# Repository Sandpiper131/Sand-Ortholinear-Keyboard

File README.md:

# [ Description ]
The Sand Ortholinear is a QWERTY style keyboard with 47 individually programmable keys. The
keyboard is powered by an ATMEGA32U4 microcontroller running the QMK open source keyboard
firmware. The goal of this project was to design a keyboard which is compact and durable while
having a simple case.

# [ Design Requirements ]
-Compact/Portable  
-Cherry MX Compatible  
-Ortholinear QWERTY (Grid) Layout with 2U spacebar  
-No visible components on top side of board  
-minimize trace presence on visible portions of top PCB  
-Sandwich style case PCB|ACRYLIC|PCB held together with M3 Screws  
-USB-C Connector  
-Sturdy Construction  

# [ Gallery ]
## Renders:
")  
")  

## Schematics:

## Board Layout:
")
")
")
")

## Pictures:

# [ Version History ]
## QMKDEVBRD
The QMK Development Board is a 3x3 Cherry MX-Compatible keypad used to
prototype a keyboard circuit prior to building a larger and more expensive keyboard. 
In addition to the basic microcontroller circuit with ISP and USB connectivity a 
prototyping area with breakouts for unused uC pins is included. Doing so 
makes this board not only a prototype for a final keyboard design, but also
a useful tool for contributing to the QMK Firmware project in the future.
The QMK Development Board functions as expected and works flawlessly with 
the QMK firmware. 

## Sand v1.0
Error in USB-C Circuit, no resistors for orientation, D+/D- not shorted 
to respective pair; USB connectivity non-functional. Added protection
circuit with Schottkey Diode and PTC fuse. Diodes are too small and
difficult to solder resulting in feedback in keyboard matrix. Crystal
Oscillator is also too small and impossible to solder by hand; Resolved
using a through hole crystal soldered onto pads. 

Changing focus to the mechanical/visual design of the keyboard is a simple
yet elegant PCB and Acrylic sandwich all held togetherwith M3 bolts and nuts.  
The resulting keyboard exceeded expectations and is very rigid, low-profile,
and provides ample protection from dust and debris.

## Sand v1.1
Added larger surface mount crystal oscillator and corrected above mentioned
flaws in the USB-C circuit. Opted not to change the diodes
as this was a minor revision and the part had already been ordered in excess.

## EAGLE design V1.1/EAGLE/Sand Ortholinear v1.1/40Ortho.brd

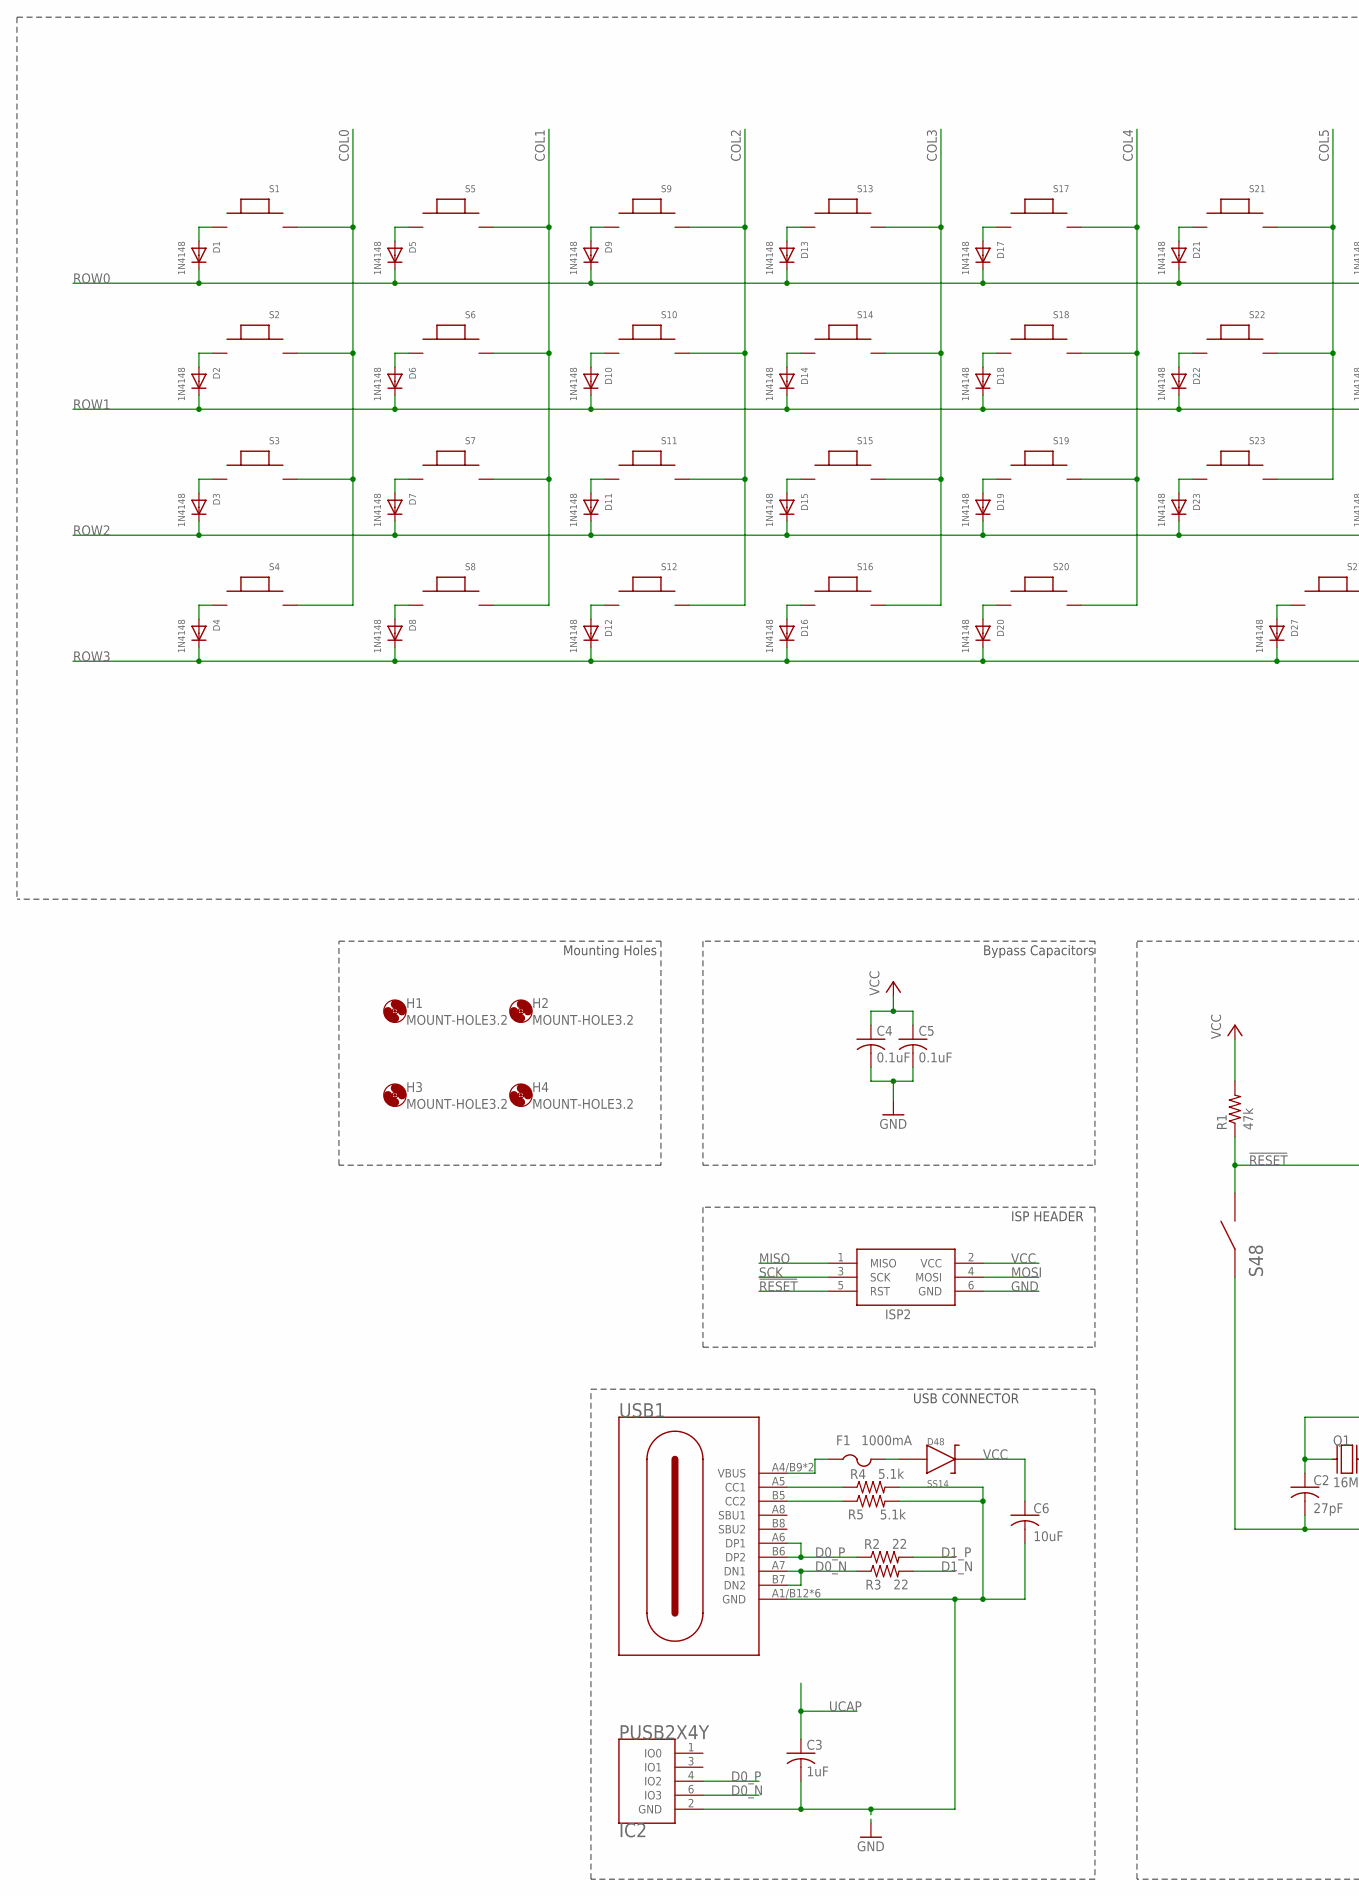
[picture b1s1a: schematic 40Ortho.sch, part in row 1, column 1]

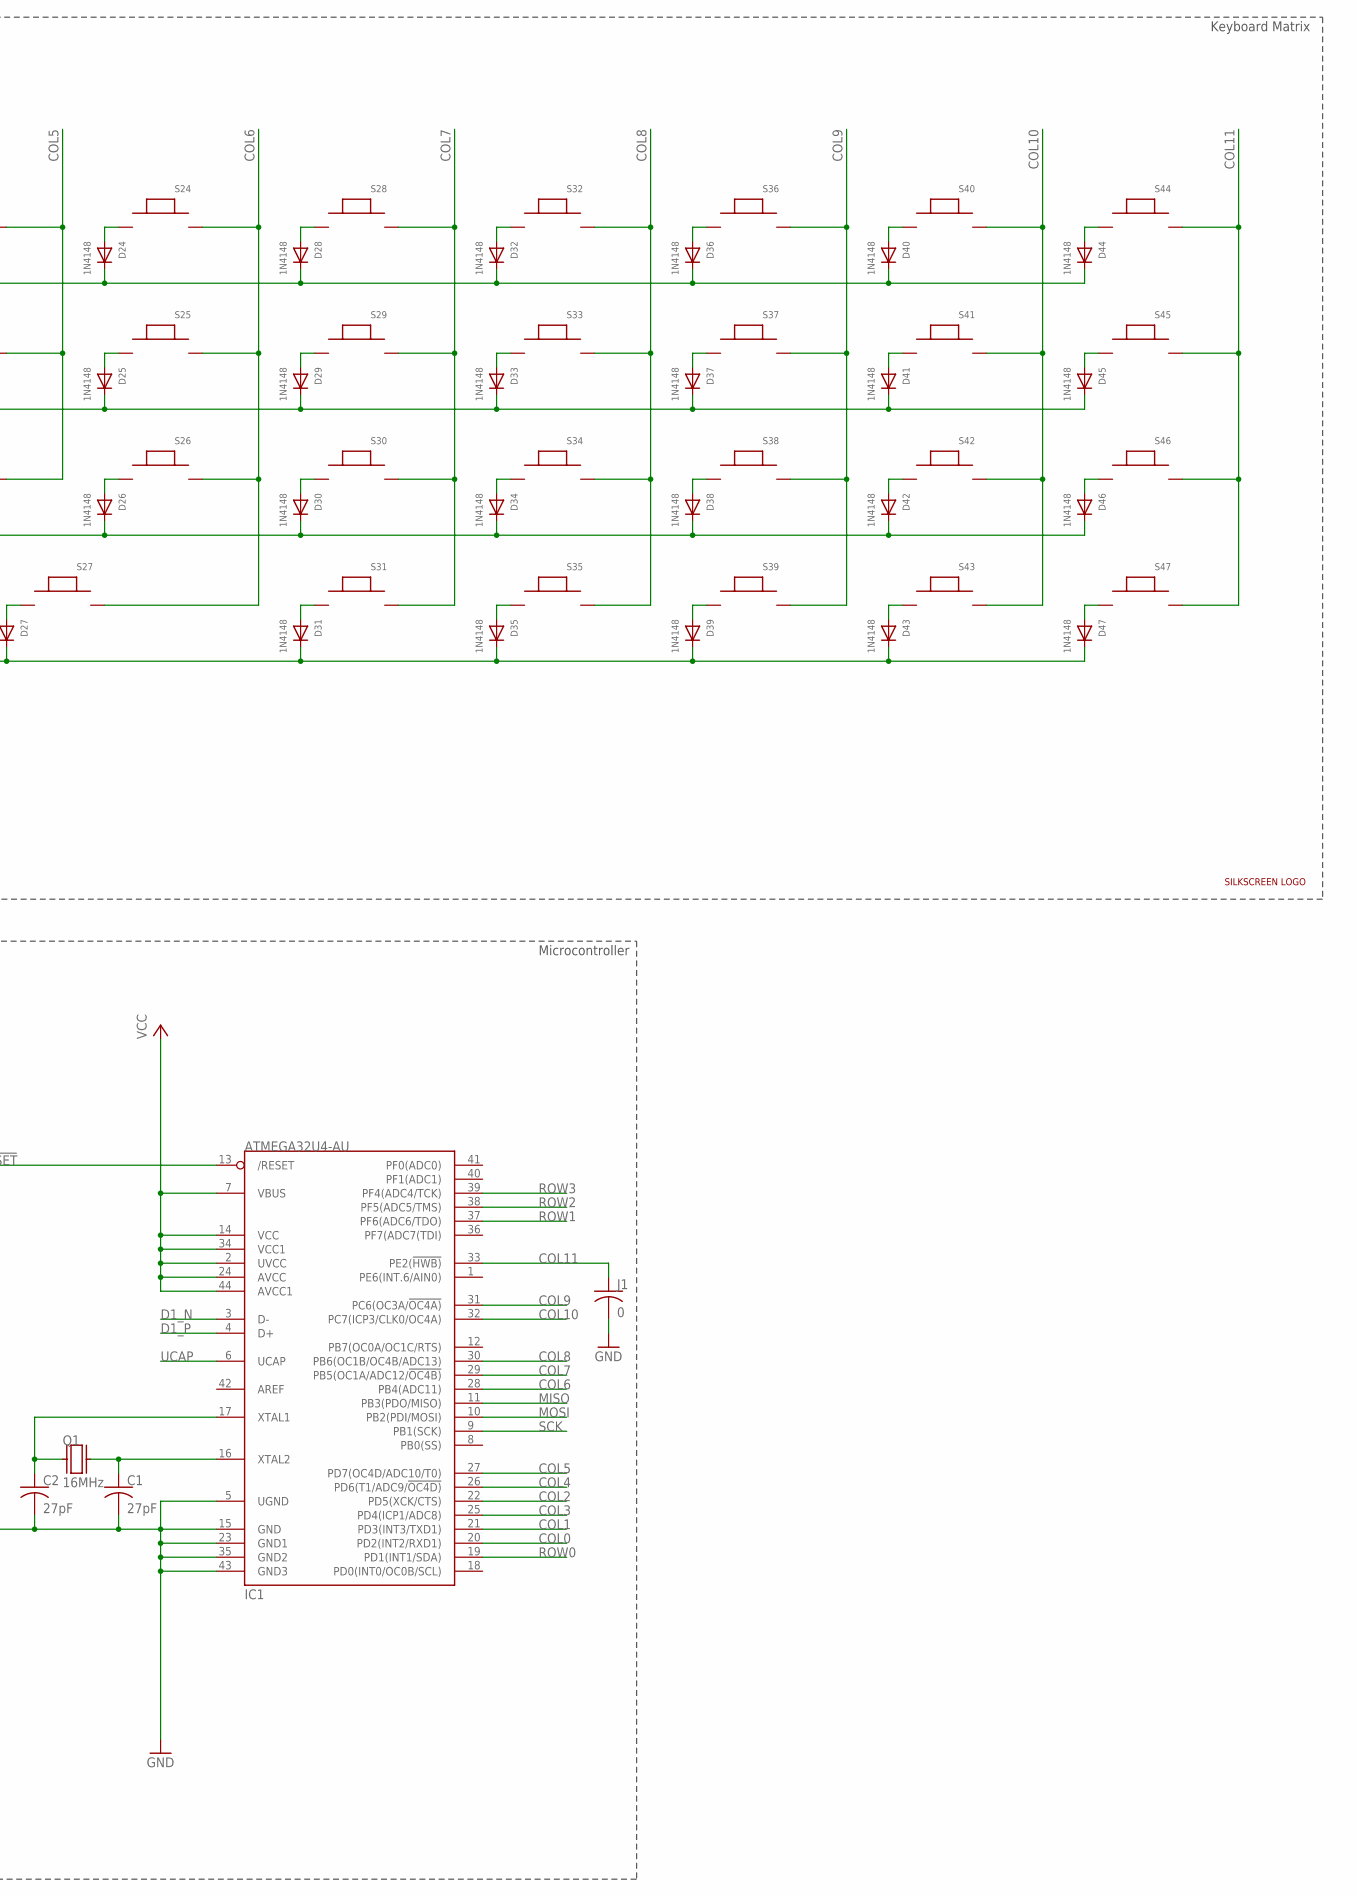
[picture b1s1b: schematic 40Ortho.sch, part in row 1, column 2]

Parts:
C1, C2: 27pF; C0805
C3: 1uF; C0805
C4, C5: 0.1uF; C0805
C6: 10uF; C0805
D1, D2, D3, D4, D5, D6, D7, D8, D9, D10, D11, D12, D13, D14, D15, D16, D17, D18, D19, D20, D21, D22, D23, D24, D25, D26, D27, D28, D29, D30, D31, D32, D33, D34, D35, D36, D37, D38, D39, D40, D41, D42, D43, D44, D45, D46, D47: 1N4148; SOD-323F
D48: SS14; DO-214AC
F1: 1000mA; R1206
H1, H2, H3, H4: MOUNT-HOLE3.2; 3,2
IC1: ATMEGA32U4-AU; TQFP44
IC2: PUSB2X4Y; SOT363
ISP2: AVRISP-6; AVRISP
J1: 0; C0805
Q1: 16MHz; ABLS7M2
R1: 47k; R0805
R2, R3: 22; R0805
R4, R5: 5.1k; R0805
S1, S2, S3, S4, S5, S6, S7, S8, S9, S10, S11, S12, S13, S14, S15, S16, S17, S18, S19, S20, S21, S22, S23, S24, S25, S26, S28, S29, S30, S31, S32, S33, S34, S35, S36, S37, S38, S39, S40, S41, S42, S43, S44, S45, S46, S47: MX_SMD_1U; MX_SMD
S27: MX_SMD_2UH; MX_SMD2U
S48: B3U-1000P
U$1: LOGO
USB1: USBC_16PINSMD

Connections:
!RESET: IC1.13 (/RESET), ISP2.5 (RST), R1.1, S48.2
COL0: IC1.20 (PD2(INT2/RXD1)), S1.P$2, S2.P$2, S3.P$2, S4.P$2
COL1: IC1.21 (PD3(INT3/TXD1)), S5.P$2, S6.P$2, S7.P$2, S8.P$2
COL2: IC1.22 (PD5(XCK/CTS)), S9.P$2, S10.P$2, S11.P$2, S12.P$2
COL3: IC1.25 (PD4(ICP1/ADC8)), S13.P$2, S14.P$2, S15.P$2, S16.P$2
COL4: IC1.26 (PD6(T1/ADC9/!OC4D)), S17.P$2, S18.P$2, S19.P$2, S20.P$2
COL5: IC1.27 (PD7(OC4D/ADC10/T0)), S21.P$2, S22.P$2, S23.P$2
COL6: IC1.28 (PB4(ADC11)), S24.P$2, S25.P$2, S26.P$2, S27.P$2
COL7: IC1.29 (PB5(OC1A/ADC12/!OC4B)), S28.P$2, S29.P$2, S30.P$2, S31.P$2
COL8: IC1.30 (PB6(OC1B/OC4B/ADC13)), S32.P$2, S33.P$2, S34.P$2, S35.P$2
COL9: IC1.31 (PC6(OC3A/!OC4A)), S36.P$2, S37.P$2, S38.P$2, S39.P$2
COL10: IC1.32 (PC7(ICP3/CLK0/OC4A)), S40.P$2, S41.P$2, S42.P$2, S43.P$2
COL11: IC1.33 (PE2(!HWB)), J1.1, S44.P$2, S45.P$2, S46.P$2, S47.P$2
D0_N: IC2.6 (IO3), R3.1, USB1.A7 (DN1), USB1.B7 (DN2)
D0_P: IC2.4 (IO2), R2.1, USB1.A6 (DP1), USB1.B6 (DP2)
D1_N: IC1.3 (D-), R3.2
D1_P: IC1.4 (D+), R2.2
GND: C1.2, C2.2, C3.2, C4.2, C5.2, C6.2, IC1.5 (UGND), IC1.15 (GND), IC1.23 (GND1), IC1.35 (GND2), IC1.43 (GND3), IC2.2 (GND), ISP2.6 (GND), J1.2, R4.2, R5.2, S48.1, USB1.A1/B12 (GND), USB1.B1/A12 (GND), USB1.GND@1 (GND), USB1.GND@2 (GND), USB1.GND@3 (GND), USB1.GND@4 (GND)
MISO: IC1.11 (PB3(PDO/MISO)), ISP2.1 (MISO)
MOSI: IC1.10 (PB2(PDI/MOSI)), ISP2.4 (MOSI)
unnamed: D32.A, S32.P$1
unnamed: D33.A, S33.P$1
unnamed: D34.A, S34.P$1
unnamed: D35.A, S35.P$1
unnamed: D36.A, S36.P$1
unnamed: D37.A, S37.P$1
unnamed: D38.A, S38.P$1
unnamed: D8.A, S8.P$1
unnamed: D40.A, S40.P$1
unnamed: D1.A, S1.P$1
unnamed: D2.A, S2.P$1
unnamed: D3.A, S3.P$1
unnamed: D4.A, S4.P$1
unnamed: D41.A, S41.P$1
unnamed: D5.A, S5.P$1
unnamed: D6.A, S6.P$1
unnamed: D9.A, S9.P$1
unnamed: D10.A, S10.P$1
unnamed: D7.A, S7.P$1
unnamed: D12.A, S12.P$1
unnamed: D42.A, S42.P$1
unnamed: D11.A, S11.P$1
unnamed: F1.1, USB1.A4/B9 (VBUS), USB1.B4/A9 (VBUS)
unnamed: D39.A, S39.P$1
unnamed: D13.A, S13.P$1
unnamed: D14.A, S14.P$1
unnamed: D15.A, S15.P$1
unnamed: D16.A, S16.P$1
unnamed: D44.A, S44.P$1
unnamed: D17.A, S17.P$1
unnamed: D18.A, S18.P$1
unnamed: D19.A, S19.P$1
unnamed: D20.A, S20.P$1
unnamed: D45.A, S45.P$1
unnamed: D21.A, S21.P$1
unnamed: D22.A, S22.P$1
unnamed: D23.A, S23.P$1
unnamed: D48.1 (ANODE), F1.2
unnamed: D46.A, S46.P$1
unnamed: D24.A, S24.P$1
unnamed: D25.A, S25.P$1
unnamed: D26.A, S26.P$1
unnamed: R4.1, USB1.A5 (CC1)
unnamed: D28.A, S28.P$1
unnamed: D29.A, S29.P$1
unnamed: D30.A, S30.P$1
unnamed: D31.A, S31.P$1
unnamed: R5.1, USB1.B5 (CC2)
unnamed: D27.A, S27.P$1
unnamed: D43.A, S43.P$1
unnamed: D47.A, S47.P$1
ROW0: D1.C, D5.C, D9.C, D13.C, D17.C, D21.C, D24.C, D28.C, D32.C, D36.C, D40.C, D44.C, IC1.19 (PD1(INT1/SDA))
ROW1: D2.C, D6.C, D10.C, D14.C, D18.C, D22.C, D25.C, D29.C, D33.C, D37.C, D41.C, D45.C, IC1.37 (PF6(ADC6/TDO))
ROW2: D3.C, D7.C, D11.C, D15.C, D19.C, D23.C, D26.C, D30.C, D34.C, D38.C, D42.C, D46.C, IC1.38 (PF5(ADC5/TMS))
ROW3: D4.C, D8.C, D12.C, D16.C, D20.C, D27.C, D31.C, D35.C, D39.C, D43.C, D47.C, IC1.39 (PF4(ADC4/TCK))
SCK: IC1.9 (PB1(SCK)), ISP2.3 (SCK)
UCAP: C3.1, IC1.6 (UCAP)
VCC: C4.1, C5.1, C6.1, D48.2 (CATHODE), IC1.2 (UVCC), IC1.7 (VBUS), IC1.14 (VCC), IC1.24 (AVCC), IC1.34 (VCC1), IC1.44 (AVCC1), ISP2.2 (VCC), R1.2
XTAL1: C2.1, IC1.17 (XTAL1), Q1.X1
XTAL2: C1.1, IC1.16 (XTAL2), Q1.X2

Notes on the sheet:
USB CONNECTOR
ISP HEADER
Microcontroller
Bypass Capacitors
Keyboard Matrix
Mounting Holes

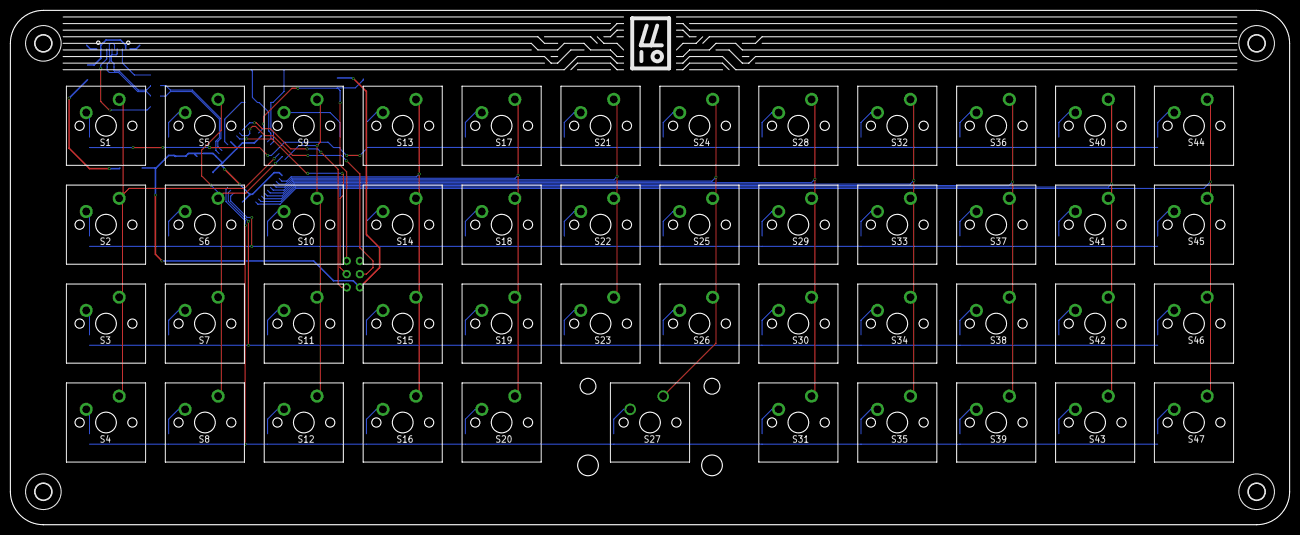
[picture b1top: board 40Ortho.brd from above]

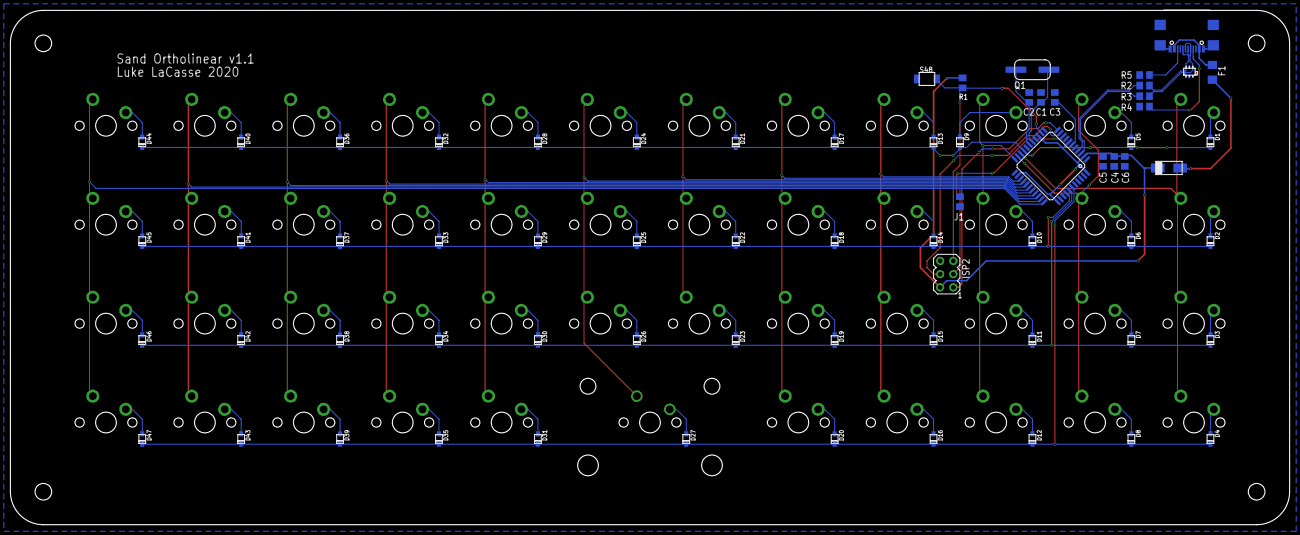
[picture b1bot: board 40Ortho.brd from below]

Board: 2 copper layers, 246.4 x 99.1 mm, 119 parts (67 on the bottom side), 80 nets.

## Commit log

2021-08-03 Set theme jekyll-theme-minimal
